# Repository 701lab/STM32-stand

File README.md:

# STM32 stand

В этом репозитории хранятся все исходные файлы печатных плат для лабораторного стенда по программированию STM32, разработанного в БГУИР.

Печатные платы разрабатывались с использованием Autodesk Eagle 9.6.1.

Кроме исходных файлов в данном репозитории можно также найти:
* файлы для заказа печатных плат;
* файлы для сборки печатных плат;
* документацию на платы оформленную почти под ЕСКД.

Данные файлы распространяются свободно и могут быть свободно использованы.

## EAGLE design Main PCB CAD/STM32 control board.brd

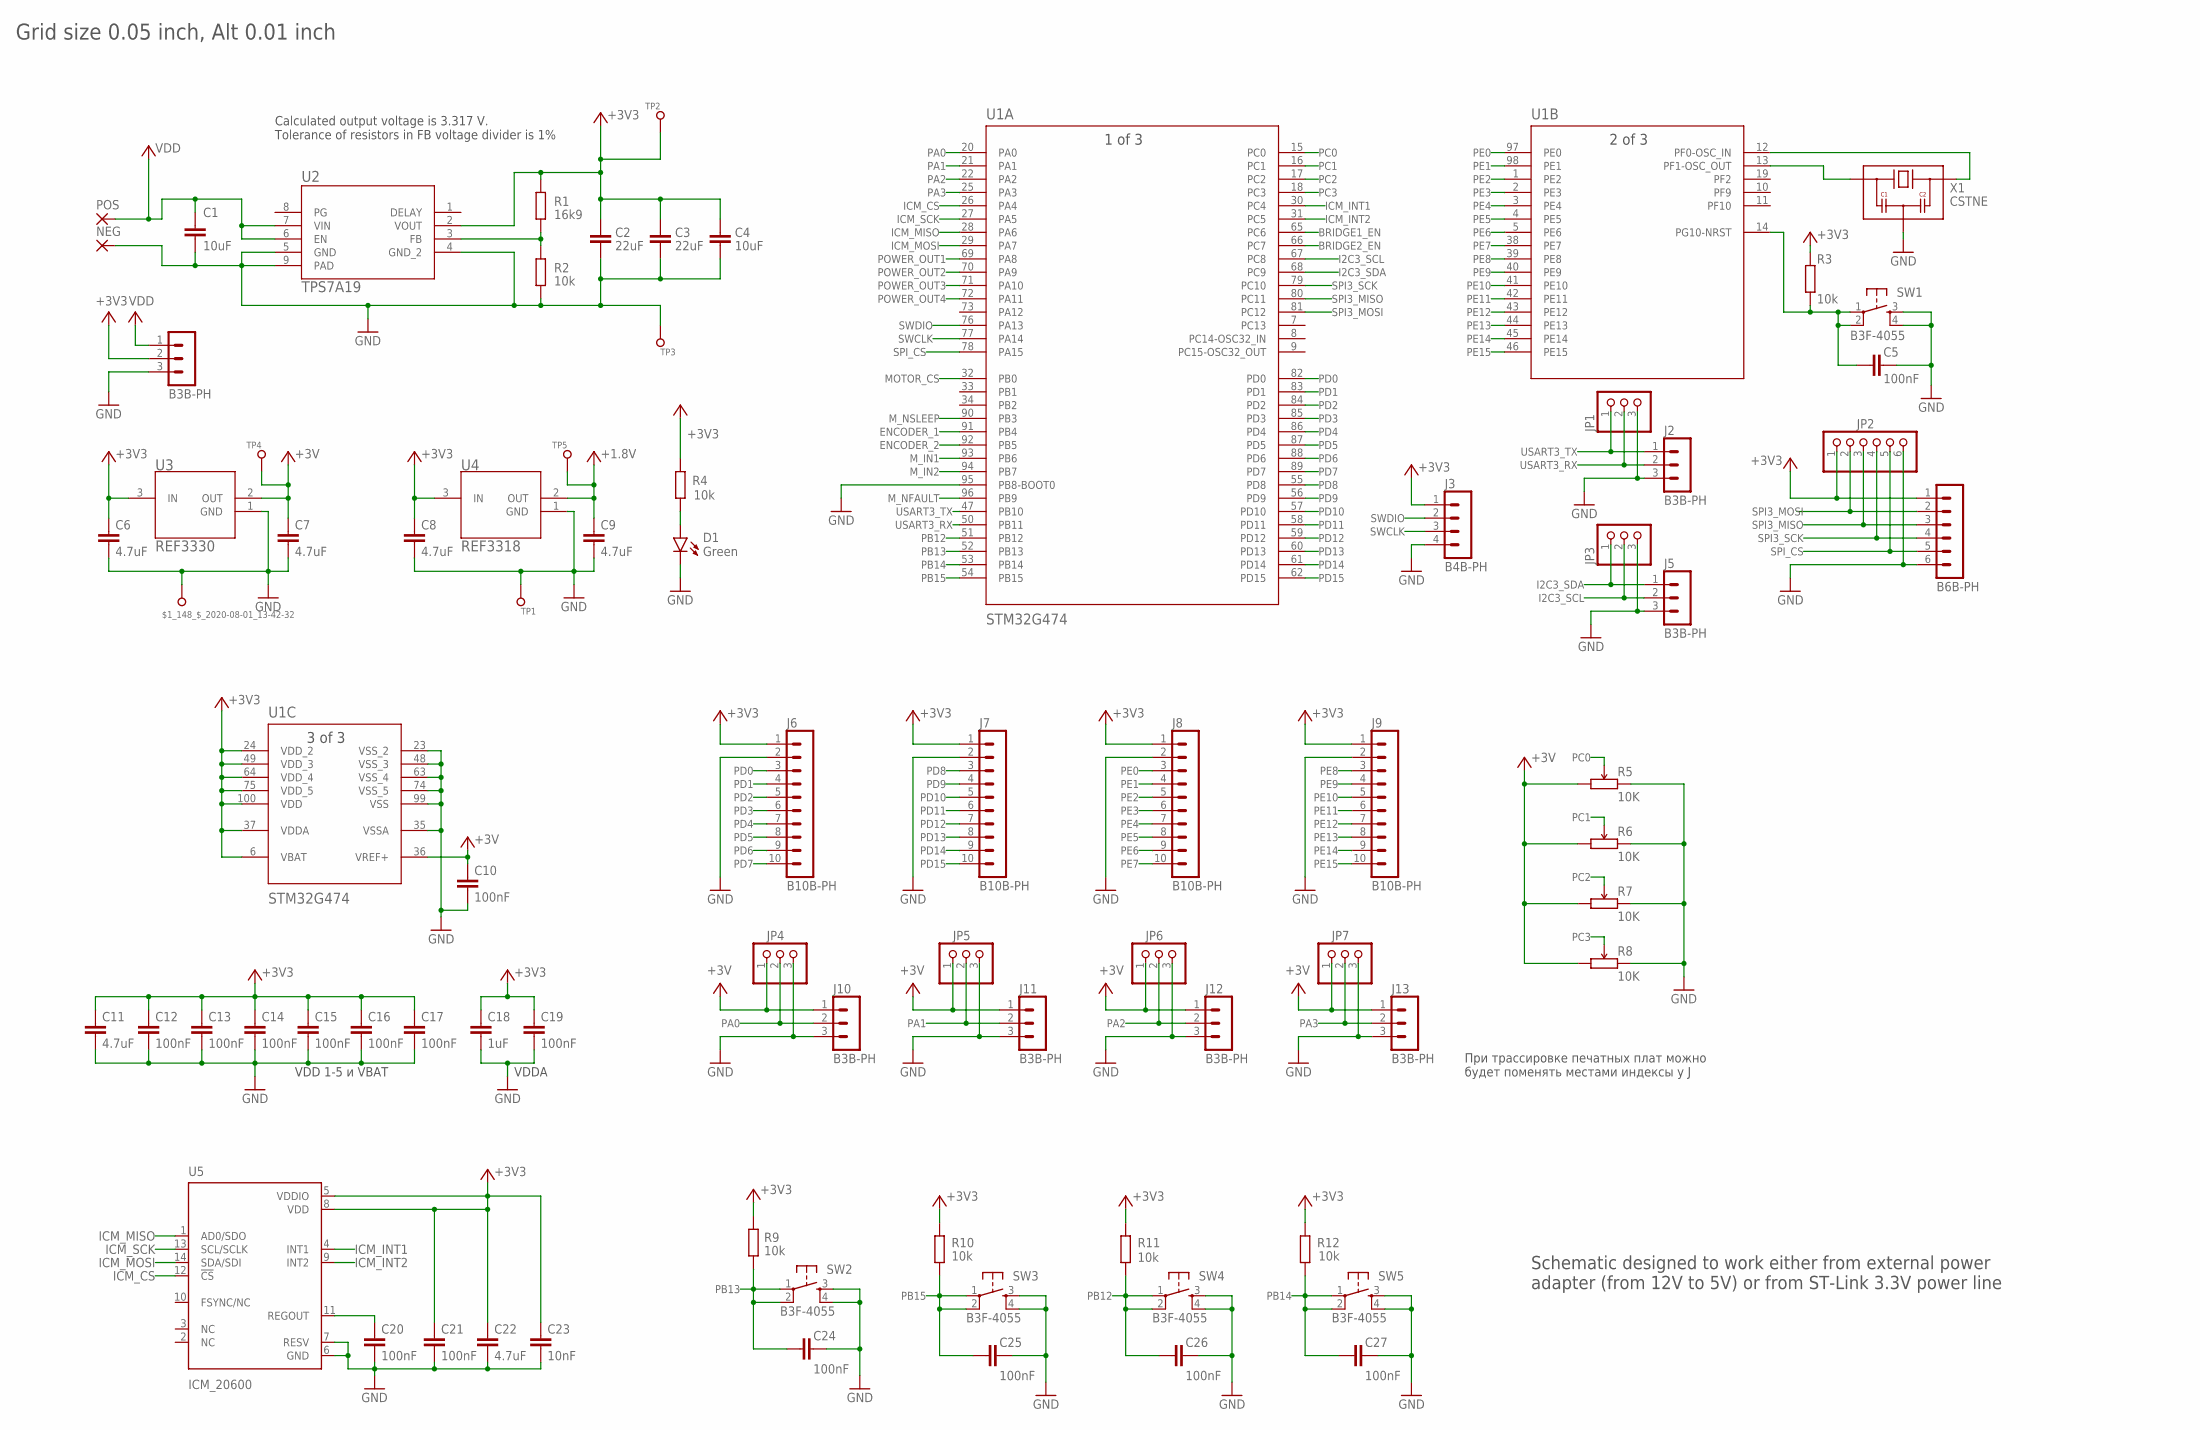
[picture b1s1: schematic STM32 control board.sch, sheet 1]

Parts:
$1_148_$_2020-08-01_13-42-32: TEST_PAD-[1.27MM_SK]; TP1.27MM_MASK_SILKSCREEN
C1, C4: 10uF; C1206; MANUFACTURER_PART_NUMBER CL31B106KAHNNNE
C2, C3: 22uF; C1210; MANUFACTURER_PART_NUMBER GRM32ER61C476ME15L
C5, C10, C12, C13, C14, C15, C16, C17, C19, C20, C21, C24, C25, C26, C27: 100nF; C0402
C6, C7, C8, C9, C11, C22: 4.7uF; C0603
C18: 1uF; C0603
C23: 10nF; C0402
D1: Green; LED-0805
J1, J2, J5, J10, J11, J12, J13: B3B-PH; B3B-PH-K
J3: B4B-PH; B4B-PH-K
J4: B6B-PH; B6B-PH-K
J6, J7, J8, J9: B10B-PH; B10B-PH-K
JP1, JP3, JP4, JP5, JP6, JP7: PINHD-1X3; 1X03
JP2: PINHD-1X6-OCT; 1X06
NEG: SMD_PAD
POS: SMD_PAD
R1: 16k9; R0402
R2, R3, R4, R9, R10, R11, R12: 10k; R0402
R5, R6, R7, R8: 10K; ALPS_PTM_LONG
SW1, SW2, SW3, SW4, SW5: B3F-4055; SWITCH_B3F-4055
TP1, TP2, TP3, TP5: 1.8; TP1.27MM_MASK_SILKSCREEN
TP4: 3.0; TP1.27MM_MASK_SILKSCREEN
U1: STM32G474; LPQFP-100
U2: TPS7A19; DRB0008B
U3: REF3330; SOT-23-3
U4: REF3318; SOT-23-3
U5: ICM_20600; 14_PIN_LGA
X1: CSTNE; MURATA_SMD_3P

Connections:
+1.8V: C9.1, TP5.1, U4.2 (OUT); also elsewhere on the board
+3V: C7.1, C10.1, J10.1, J11.1, J12.1, J13.1, JP4.1, JP5.1, JP6.1, JP7.1, R5.P$1 (1), R6.P$1 (1), R7.P$1 (1), R8.P$1 (1), TP4.1, U1.36 (VREF+), U3.2 (OUT)
+3V3: C2.1, C3.1, C4.1, C6.1, C8.1, C11.1, C12.1, C13.1, C14.1, C15.1, C16.1, C17.1, C18.1, C19.1, C21.1, C22.1, C23.1, J1.2, J3.1, J4.1, J6.1, J7.1, J8.1, J9.1, JP2.1, R1.2, R3.1, R4.2, R9.2, R10.2, R11.2, R12.2, TP2.1, U1.6 (VBAT), U1.24 (VDD_2), U1.37 (VDDA), U1.49 (VDD_3), U1.64 (VDD_4), U1.75 (VDD_5), U1.100 (VDD), U2.2 (VOUT), U3.3 (IN), U4.3 (IN), U5.5 (VDDIO), U5.8 (VDD); also elsewhere on the board
BRIDGE1_EN: U1.65 (PC6); also elsewhere on the board
BRIDGE2_EN: U1.66 (PC7); also elsewhere on the board
ENCODER_1: U1.91 (PB4); also elsewhere on the board
ENCODER_2: U1.92 (PB5); also elsewhere on the board
GND: $1_148_$_2020-08-01_13-42-32.1, C1.2, C2.2, C3.2, C4.2, C5.2, C6.2, C7.2, C8.2, C9.2, C10.2, C11.2, C12.2, C13.2, C14.2, C15.2, C16.2, C17.2, C18.2, C19.2, C20.2, C21.2, C22.2, C23.2, C24.2, C25.2, C26.2, C27.2, D1.- (C), J1.3, J2.3, J3.4, J4.6, J5.3, J6.2, J7.2, J8.2, J9.2, J10.3, J11.3, J12.3, J13.3, JP1.3, JP2.6, JP3.3, JP4.3, JP5.3, JP6.3, JP7.3, NEG.1, R2.1, R5.P$3 (3), R6.P$3 (3), R7.P$3 (3), R8.P$3 (3), SW1.3, SW1.4, SW2.3, SW2.4, SW3.3, SW3.4, SW4.3, SW4.4, SW5.3, SW5.4, TP1.1, TP3.1, U1.23 (VSS_2), U1.35 (VSSA), U1.48 (VSS_3), U1.63 (VSS_4), U1.74 (VSS_5), U1.95 (PB8-BOOT0), U1.99 (VSS), U2.4 (GND_2), U2.5 (GND), U2.9 (PAD), U3.1 (GND), U4.1 (GND), U5.6 (GND), U5.7 (RESV), X1.2 (GND); also elsewhere on the board
I2C3_SCL: J5.2, JP3.2, U1.67 (PC8)
I2C3_SDA: J5.1, JP3.1, U1.68 (PC9)
ICM_CS: U1.26 (PA4), U5.12 (!CS)
ICM_INT1: U1.30 (PC4), U5.4 (INT1)
ICM_INT2: U1.31 (PC5), U5.9 (INT2)
ICM_MISO: U1.28 (PA6), U5.1 (AD0/SDO)
ICM_MOSI: U1.29 (PA7), U5.14 (SDA/SDI)
ICM_SCK: U1.27 (PA5), U5.13 (SCL/SCLK)
MOTOR_CS: U1.32 (PB0); also elsewhere on the board
M_IN1: U1.93 (PB6); also elsewhere on the board
M_IN2: U1.94 (PB7); also elsewhere on the board
M_NFAULT: U1.96 (PB9); also elsewhere on the board
M_NSLEEP: U1.90 (PB3); also elsewhere on the board
unnamed: U1.12 (PF0-OSC_IN), X1.3 (OUT)
unnamed: U1.13 (PF1-OSC_OUT), X1.1 (IN)
unnamed: D1.+ (A), R4.1
unnamed: R1.1, R2.2, U2.3 (FB)
PA0: J10.2, JP4.2, U1.20 (PA0)
PA1: J11.2, JP5.2, U1.21 (PA1)
PA2: J12.2, JP6.2, U1.22 (PA2)
PA3: J13.2, JP7.2, U1.25 (PA3)
PB12: C26.1, R11.1, SW4.1, SW4.2, U1.51 (PB12)
PB13: C24.1, R9.1, SW2.1, SW2.2, U1.52 (PB13)
PB14: C27.1, R12.1, SW5.1, SW5.2, U1.53 (PB14)
PB15: C25.1, R10.1, SW3.1, SW3.2, U1.54 (PB15)
PC0: R5.P$2 (2), U1.15 (PC0)
PC1: R6.P$2 (2), U1.16 (PC1)
PC2: R7.P$2 (2), U1.17 (PC2)
PC3: R8.P$2 (2), U1.18 (PC3)
PD0: J6.3, U1.82 (PD0); also elsewhere on the board
PD1: J6.4, U1.83 (PD1); also elsewhere on the board
PD2: J6.5, U1.84 (PD2); also elsewhere on the board
PD3: J6.6, U1.85 (PD3); also elsewhere on the board
PD4: J6.7, U1.86 (PD4); also elsewhere on the board
PD5: J6.8, U1.87 (PD5); also elsewhere on the board
PD6: J6.9, U1.88 (PD6); also elsewhere on the board
PD7: J6.10, U1.89 (PD7); also elsewhere on the board
PD8: J7.3, U1.55 (PD8); also elsewhere on the board
PD9: J7.4, U1.56 (PD9); also elsewhere on the board
PD10: J7.5, U1.57 (PD10); also elsewhere on the board
PD11: J7.6, U1.58 (PD11); also elsewhere on the board
PD12: J7.7, U1.59 (PD12); also elsewhere on the board
PD13: J7.8, U1.60 (PD13); also elsewhere on the board
PD14: J7.9, U1.61 (PD14); also elsewhere on the board
PD15: J7.10, U1.62 (PD15); also elsewhere on the board
PE0: J8.3, U1.97 (PE0); also elsewhere on the board
PE1: J8.4, U1.98 (PE1); also elsewhere on the board
PE2: J8.5, U1.1 (PE2); also elsewhere on the board
PE3: J8.6, U1.2 (PE3); also elsewhere on the board
PE4: J8.7, U1.3 (PE4); also elsewhere on the board
PE5: J8.8, U1.4 (PE5); also elsewhere on the board
PE6: J8.9, U1.5 (PE6); also elsewhere on the board
PE7: J8.10, U1.38 (PE7); also elsewhere on the board
PE8: J9.3, U1.39 (PE8); also elsewhere on the board
PE9: J9.4, U1.40 (PE9); also elsewhere on the board
PE10: J9.5, U1.41 (PE10); also elsewhere on the board
PE11: J9.6, U1.42 (PE11); also elsewhere on the board
PE12: J9.7, U1.43 (PE12); also elsewhere on the board
PE13: J9.8, U1.44 (PE13); also elsewhere on the board
PE14: J9.9, U1.45 (PE14); also elsewhere on the board
PE15: J9.10, U1.46 (PE15); also elsewhere on the board
POWER_OUT1: U1.69 (PA8); also elsewhere on the board
POWER_OUT2: U1.70 (PA9); also elsewhere on the board
POWER_OUT3: U1.71 (PA10); also elsewhere on the board
POWER_OUT4: U1.72 (PA11); also elsewhere on the board
REG: C20.1, U5.11 (REGOUT)
RST: C5.1, R3.2, SW1.1, SW1.2, U1.14 (PG10-NRST)
SPI3_MISO: J4.3, JP2.3, U1.80 (PC11)
SPI3_MOSI: J4.2, JP2.2, U1.81 (PC12)
SPI3_SCK: J4.4, JP2.4, U1.79 (PC10)
SPI_CS: J4.5, JP2.5, U1.78 (PA15)
SWCLK: J3.3, U1.77 (PA14)
SWDIO: J3.2, U1.76 (PA13)
USART3_RX: J2.2, JP1.2, U1.50 (PB11)
USART3_TX: J2.1, JP1.1, U1.47 (PB10)
VDD: C1.1, J1.1, POS.1, U2.6 (EN), U2.7 (VIN); also elsewhere on the board

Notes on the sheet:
Grid size 0.05 inch, Alt 0.01 inch
VDD 1-5 и VBAT
VDDA
Calculated output voltage is 3.317 V. Tolerance of resistors in FB voltage divider is 1%
Schematic designed to work either from external power adapter (from 12V to 5V) or from ST-Link 3.3V power line
При трассировке печатных плат можно будет поменять местами индексы у J

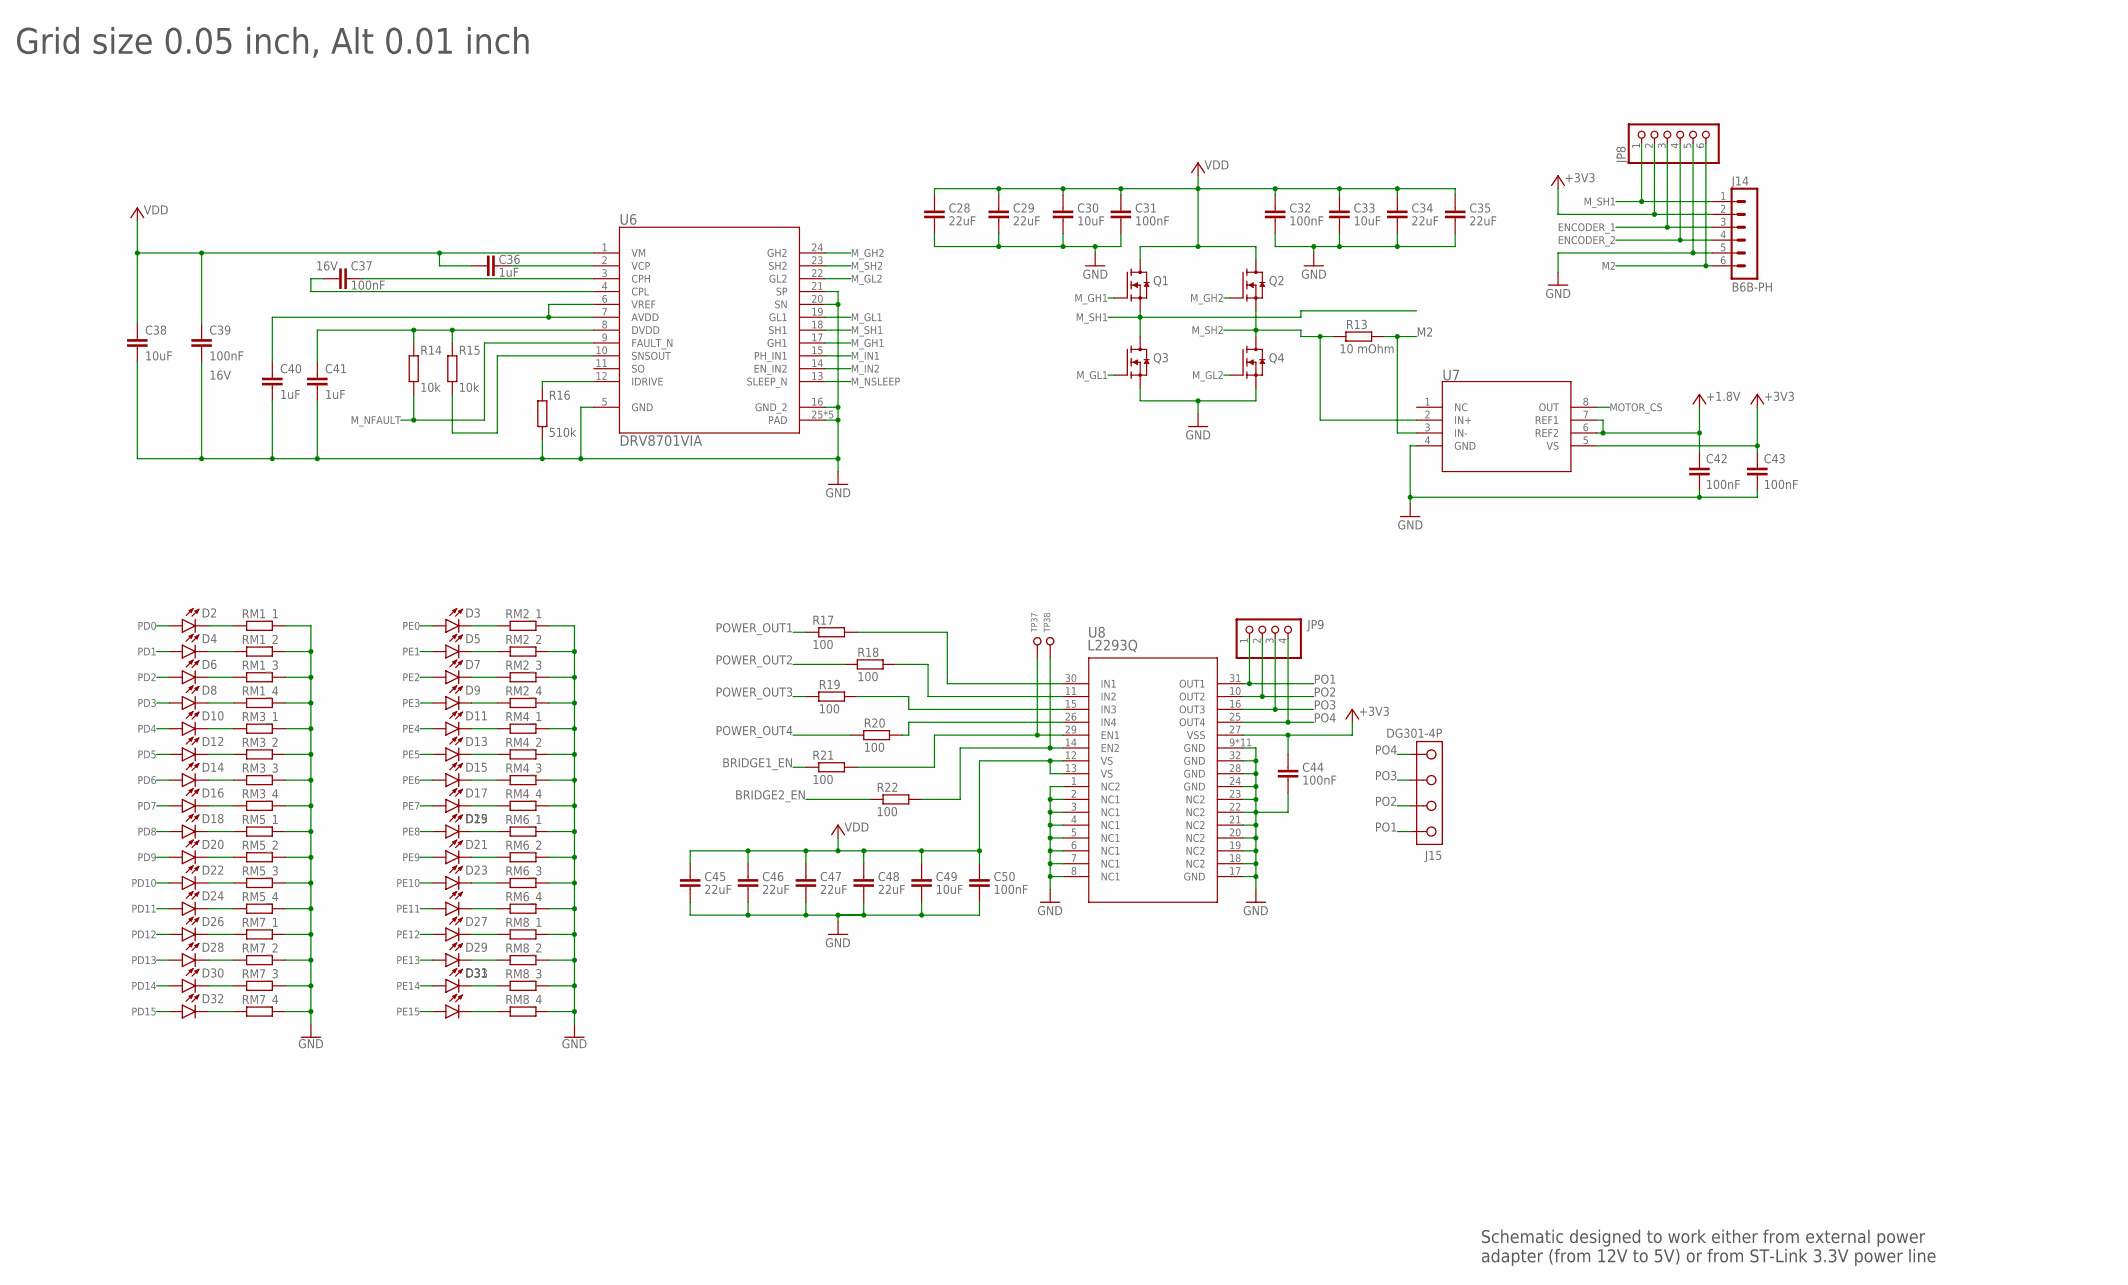
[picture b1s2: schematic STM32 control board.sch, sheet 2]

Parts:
C28, C29, C34, C35, C45, C46, C47, C48: 22uF; C1210; MANUFACTURER_PART_NUMBER GRM32ER61C476ME15L
C30, C33, C38, C49: 10uF; C1206; MANUFACTURER_PART_NUMBER CL31B106KAHNNNE
C31, C32, C37, C39, C42, C43, C44, C50: 100nF; C0402
C36, C40, C41: 1uF; C0603
D2, D3, D4, D5, D6, D7, D8, D9, D10, D11, D12, D13, D14, D15, D16, D17, D18, D19, D20, D21, D22, D23, D24, D25, D26, D27, D28, D29, D30, D31, D32, D33: Blue; LED-0805
J14: B6B-PH; B6B-PH-K
J15: DG301-4P
JP8: PINHD-1X6-OCT; 1X06
JP9: PINHD-1X4; 1X04
Q1, Q2, Q3, Q4: CSD15571Q2; SON2X2
R13: 10 mOhm; CS_R0805; MANUFACTURER_PART_NUMBER ERJ6CWDR010V
R14, R15: 10k; R0402
R16: 510k; R0402
R17, R18, R19, R20, R21, R22: 100; R0402
RM1, RM2, RM3, RM4, RM5, RM6, RM7, RM8: RES_ARRAY0603; 0603-ARC
TP37, TP38: TEST_PAD-[1.27MM_SK]; TP1.27MM_MASK_SILKSCREEN
U6: DRV8701VIA; VQFN-24-VIA
U7: INA240_TSSOP; TSSOP-8; MANUFACTURER_PART_NUMBER INA240
U8: L2293Q; QFN_293Q_STM

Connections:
+1.8V: C42.1, U7.6 (REF2), U7.7 (REF1); also elsewhere on the board
+3V3: C43.1, C44.1, J14.2, JP8.2, U7.5 (VS), U8.27 (VSS); also elsewhere on the board
AVDD1: C40.2, U6.6 (VREF), U6.7 (AVDD)
BRIDGE1_EN: R21.1; also elsewhere on the board
BRIDGE2_EN: R22.1; also elsewhere on the board
DRV2_SNSOUT: R15.1, U6.10 (SNSOUT)
DVDD2: C41.2, R14.2, R15.2, U6.8 (DVDD)
ENCODER_1: J14.3, JP8.3; also elsewhere on the board
ENCODER_2: J14.4, JP8.4; also elsewhere on the board
GND: C28.2, C29.2, C30.2, C31.2, C32.2, C33.2, C34.2, C35.2, C38.2, C39.2, C40.1, C41.1, C42.2, C43.2, C44.2, C45.2, C46.2, C47.2, C48.2, C49.2, C50.2, J14.5, JP8.5, Q3.S4 (S), Q3.S8 (S), Q4.S4 (S), Q4.S8 (S), R16.1, RM1.1, RM1.2 (1), RM1.3 (1), RM1.4 (1), RM2.1, RM2.2 (1), RM2.3 (1), RM2.4 (1), RM3.1, RM3.2 (1), RM3.3 (1), RM3.4 (1), RM4.1, RM4.2 (1), RM4.3 (1), RM4.4 (1), RM5.1, RM5.2 (1), RM5.3 (1), RM5.4 (1), RM6.1, RM6.2 (1), RM6.3 (1), RM6.4 (1), RM7.1, RM7.2 (1), RM7.3 (1), RM7.4 (1), RM8.1, RM8.2 (1), RM8.3 (1), RM8.4 (1), U6.5 (GND), U6.16 (GND_2), U6.20 (SN), U6.21 (SP), U6.25 (PAD), U6.26 (PAD), U6.27 (PAD), U6.28 (PAD), U6.29 (PAD), U7.4 (GND), U8.1 (NC2), U8.2 (NC1), U8.3 (NC1), U8.4 (NC1), U8.5 (NC1), U8.6 (NC1), U8.7 (NC1), U8.8 (NC1), U8.9 (GND), U8.17 (GND), U8.18 (NC2), U8.19 (NC2), U8.20 (NC2), U8.21 (NC2), U8.22 (NC2), U8.23 (NC2), U8.24 (GND), U8.28 (GND), U8.32 (GND), U8.P$1 (GND), U8.P$2 (GND), U8.P$3 (GND), U8.P$4 (GND), U8.P$5 (GND), U8.P$6 (GND), U8.P$7 (GND), U8.P$8 (GND), U8.P$9 (GND), U8.PAD (GND); also elsewhere on the board
M2: J14.6, JP8.6, R13.2, U7.3 (IN-)
MOTOR_CS: U7.8 (OUT); also elsewhere on the board
M_GH1: Q1.G3 (G), U6.17 (GH1)
M_GH2: Q2.G3 (G), U6.24 (GH2)
M_GL1: Q3.G3 (G), U6.19 (GL1)
M_GL2: Q4.G3 (G), U6.22 (GL2)
M_IN1: U6.15 (PH_IN1); also elsewhere on the board
M_IN2: U6.14 (EN_IN2); also elsewhere on the board
M_NFAULT: R14.1, U6.9 (FAULT_N); also elsewhere on the board
M_NSLEEP: U6.13 (SLEEP_N); also elsewhere on the board
M_SH1: J14.1, JP8.1, Q1.S4 (S), Q1.S8 (S), Q3.D1 (D), Q3.D2 (D), Q3.D5 (D), Q3.D6 (D), Q3.D7 (D), U6.18 (SH1)
M_SH2: Q2.S4 (S), Q2.S8 (S), Q4.D1 (D), Q4.D2 (D), Q4.D5 (D), Q4.D6 (D), Q4.D7 (D), R13.1, U6.23 (SH2), U7.2 (IN+)
unnamed: D16.- (C), RM3.5 (2)
unnamed: D14.- (C), RM3.6 (2)
unnamed: D12.- (C), RM3.7 (2)
unnamed: D10.- (C), RM3.8 (2)
unnamed: R17.2, U8.30 (IN1)
unnamed: D2.- (C), RM1.8 (2)
unnamed: D4.- (C), RM1.7 (2)
unnamed: D6.- (C), RM1.6 (2)
unnamed: D8.- (C), RM1.5 (2)
unnamed: R18.2, U8.11 (IN2)
unnamed: R19.2, U8.15 (IN3)
unnamed: R20.2, U8.26 (IN4)
unnamed: R21.2, TP37.1, U8.29 (EN1)
unnamed: R22.2, TP38.1, U8.14 (EN2)
unnamed: D18.- (C), RM5.8 (2)
unnamed: C37.1, U6.3 (CPH)
unnamed: D20.- (C), RM5.7 (2)
unnamed: D22.- (C), RM5.6 (2)
unnamed: D24.- (C), RM5.5 (2)
unnamed: D26.- (C), RM7.8 (2)
unnamed: D28.- (C), RM7.7 (2)
unnamed: D30.- (C), RM7.6 (2)
unnamed: D32.- (C), RM7.5 (2)
unnamed: C37.2, U6.4 (CPL)
unnamed: C36.2, U6.2 (VCP)
unnamed: D3.- (C), RM2.8 (2)
unnamed: D5.- (C), RM2.7 (2)
unnamed: D7.- (C), RM2.6 (2)
unnamed: R16.2, U6.12 (IDRIVE)
unnamed: D9.- (C), RM2.5 (2)
unnamed: D11.- (C), RM4.8 (2)
unnamed: D13.- (C), RM4.7 (2)
unnamed: D15.- (C), RM4.6 (2)
unnamed: D17.- (C), RM4.5 (2)
unnamed: D19.- (C), RM6.8 (2)
unnamed: D21.- (C), RM6.7 (2)
unnamed: D23.- (C), RM6.6 (2)
unnamed: D25.- (C), RM6.5 (2)
unnamed: D27.- (C), RM8.8 (2)
unnamed: D29.- (C), RM8.7 (2)
unnamed: D31.- (C), RM8.6 (2)
unnamed: D33.- (C), RM8.5 (2)
PD0: D2.+ (A); also elsewhere on the board
PD1: D4.+ (A); also elsewhere on the board
PD2: D6.+ (A); also elsewhere on the board
PD3: D8.+ (A); also elsewhere on the board
PD4: D10.+ (A); also elsewhere on the board
PD5: D12.+ (A); also elsewhere on the board
PD6: D14.+ (A); also elsewhere on the board
PD7: D16.+ (A); also elsewhere on the board
PD8: D18.+ (A); also elsewhere on the board
PD9: D20.+ (A); also elsewhere on the board
PD10: D22.+ (A); also elsewhere on the board
PD11: D24.+ (A); also elsewhere on the board
PD12: D26.+ (A); also elsewhere on the board
PD13: D28.+ (A); also elsewhere on the board
PD14: D30.+ (A); also elsewhere on the board
PD15: D32.+ (A); also elsewhere on the board
PE0: D3.+ (A); also elsewhere on the board
PE1: D5.+ (A); also elsewhere on the board
PE2: D7.+ (A); also elsewhere on the board
PE3: D9.+ (A); also elsewhere on the board
PE4: D11.+ (A); also elsewhere on the board
PE5: D13.+ (A); also elsewhere on the board
PE6: D15.+ (A); also elsewhere on the board
PE7: D17.+ (A); also elsewhere on the board
PE8: D19.+ (A); also elsewhere on the board
PE9: D21.+ (A); also elsewhere on the board
PE10: D23.+ (A); also elsewhere on the board
PE11: D25.+ (A); also elsewhere on the board
PE12: D27.+ (A); also elsewhere on the board
PE13: D29.+ (A); also elsewhere on the board
PE14: D31.+ (A); also elsewhere on the board
PE15: D33.+ (A); also elsewhere on the board
PO1: J15.1, JP9.1, U8.31 (OUT1)
PO2: J15.2, JP9.2, U8.10 (OUT2)
PO3: J15.3, JP9.3, U8.16 (OUT3)
PO4: J15.4, JP9.4, U8.25 (OUT4)
POWER_OUT1: R17.1; also elsewhere on the board
POWER_OUT2: R18.1; also elsewhere on the board
POWER_OUT3: R19.1; also elsewhere on the board
POWER_OUT4: R20.1; also elsewhere on the board
VDD: C28.1, C29.1, C30.1, C31.1, C32.1, C33.1, C34.1, C35.1, C36.1, C38.1, C39.1, C45.1, C46.1, C47.1, C48.1, C49.1, C50.1, Q1.D1 (D), Q1.D2 (D), Q1.D5 (D), Q1.D6 (D), Q1.D7 (D), Q2.D1 (D), Q2.D2 (D), Q2.D5 (D), Q2.D6 (D), Q2.D7 (D), U6.1 (VM), U8.12 (VS), U8.13 (VS); also elsewhere on the board

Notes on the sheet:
Grid size 0.05 inch, Alt 0.01 inch
16V
Schematic designed to work either from external power adapter (from 12V to 5V) or from ST-Link 3.3V power line

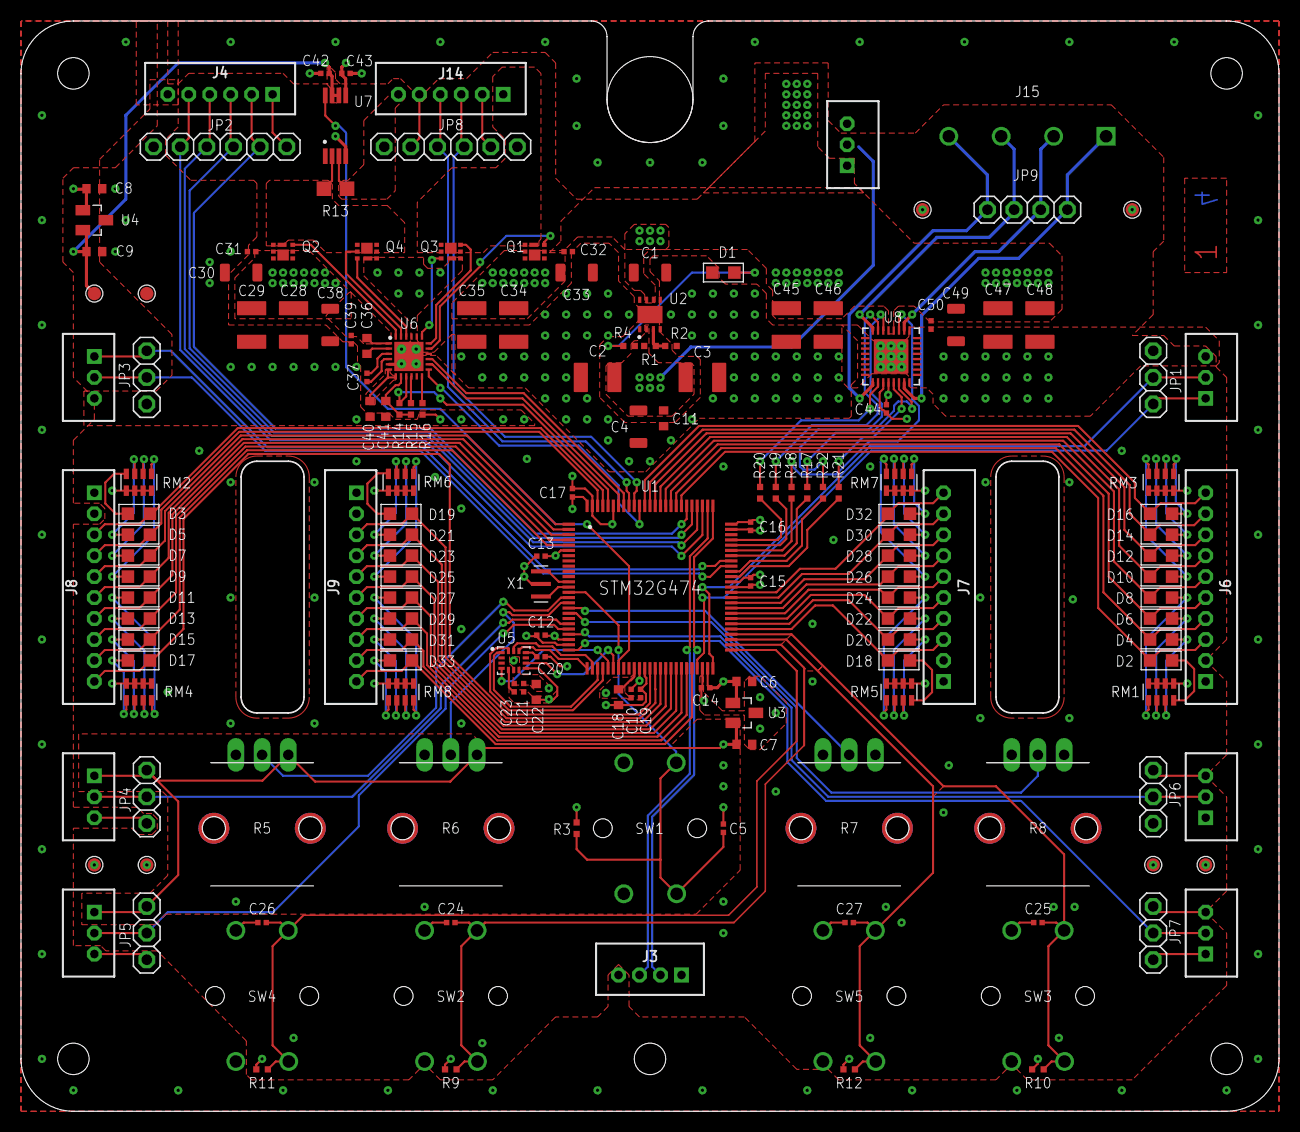
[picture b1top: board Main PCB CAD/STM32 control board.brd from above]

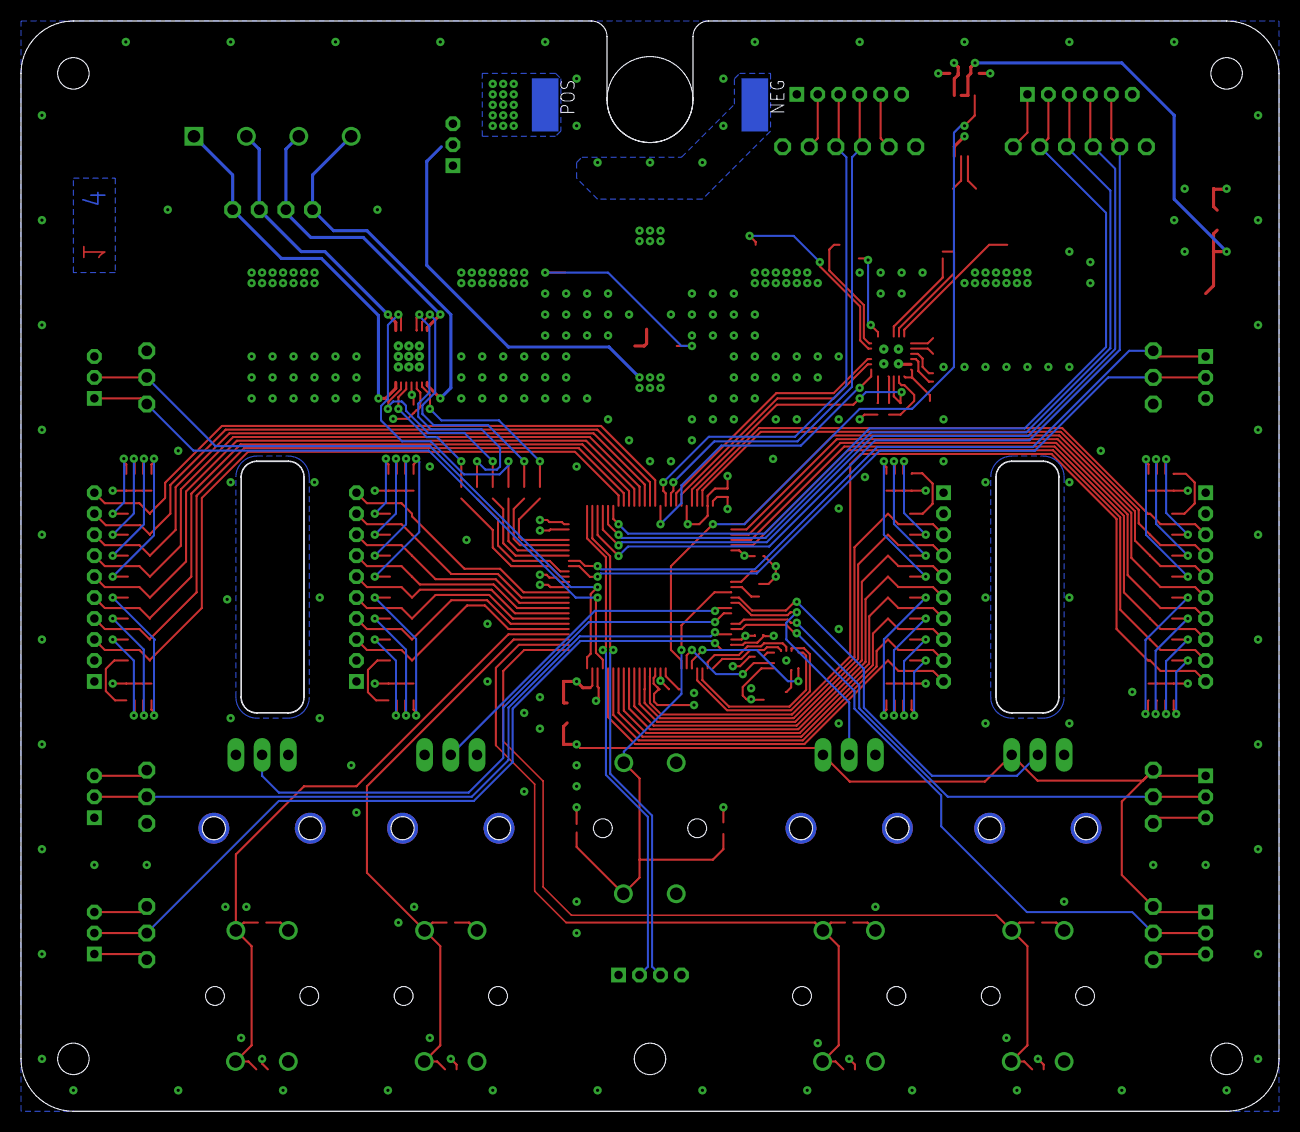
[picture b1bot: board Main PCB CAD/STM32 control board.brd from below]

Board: 4 copper layers, 120.0 x 104.0 mm, 165 parts (2 on the bottom side), 140 nets.

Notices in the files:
parts and their libraries:
con-jst-ph: Copyright (C) 2016, Bob Starr
COPYRIGHT: Copyright (C) 2018 Accelerated Designs. All rights reserved
COPYRIGHT: Copyright (C) 2016 Accelerated Designs. All rights reserved
